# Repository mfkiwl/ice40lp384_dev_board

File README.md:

The ice30lp384_dev_board project is a multi-purpose castellated board that can be used in a breadboard or as a module in other projects.

- [Programming](/docs/Programming.md)
- [Board Creation](/docs/Board_Creation.md)

The pins on the right side of the board are geared towards programming and the pins on the left are for general use.

PCBs were ordered from OSHPark.
Stencil was ordered from OSHStencil.
Parts were ordered from Mouser, see [BOM](/docs/BOM%20-Mouser%20.xlsx).

The constraint files can be found [here](/verilog_projects/config).

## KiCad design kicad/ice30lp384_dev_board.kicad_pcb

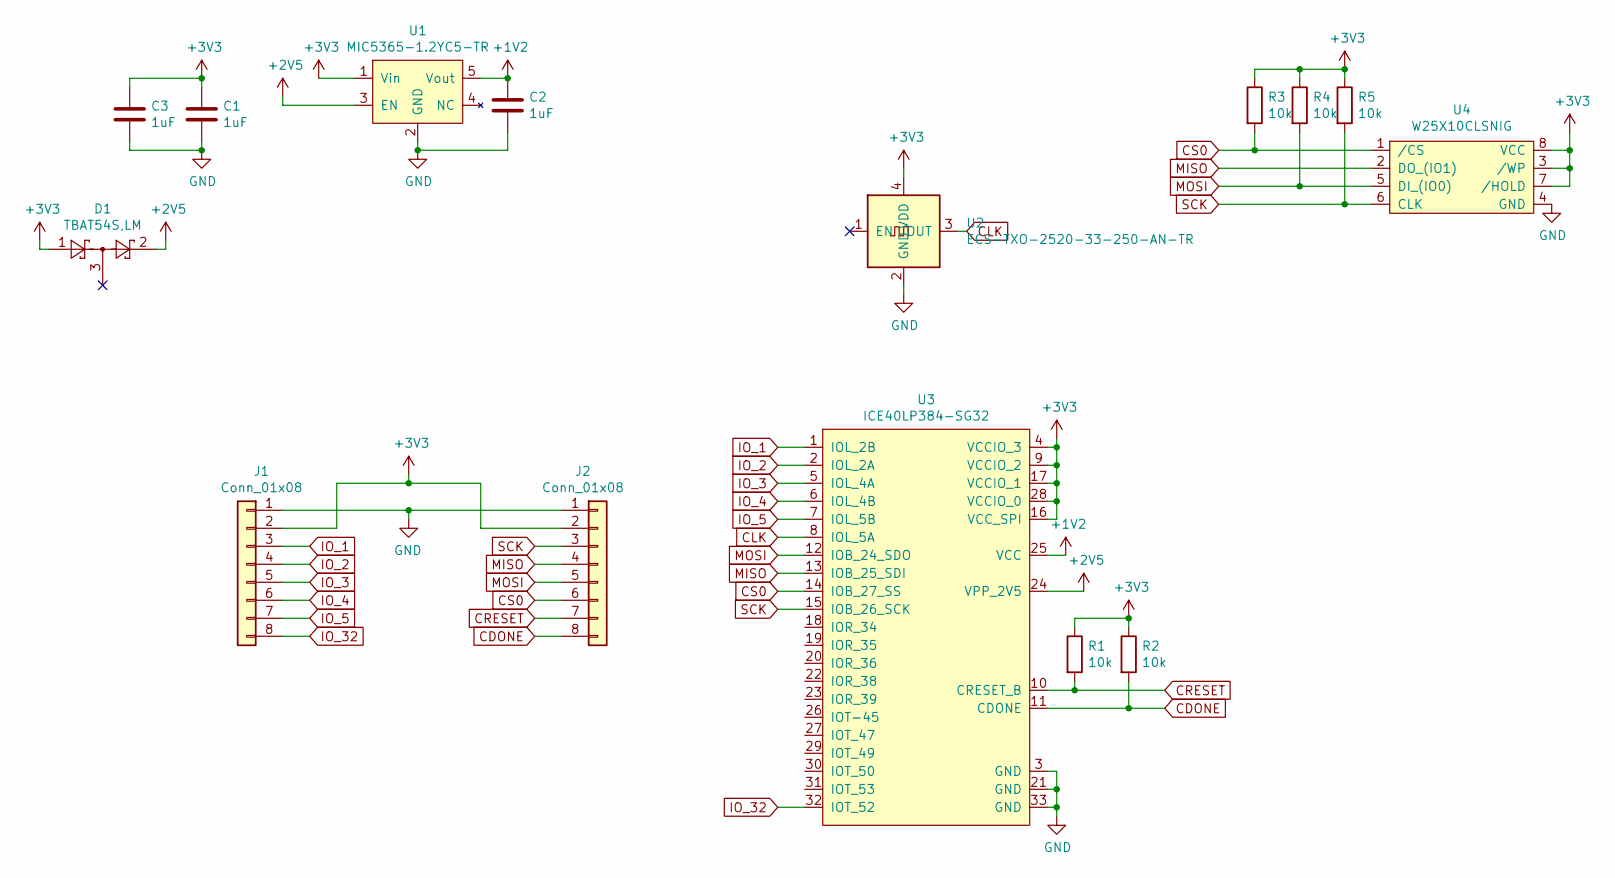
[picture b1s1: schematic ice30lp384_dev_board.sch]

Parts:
C1, C2, C3: 1uF; C_0402_1005Metric
D1: TBAT54S,LM; SOT-23
J1, J2: Conn_01x08; PinHeader_1x08_P2.54mm_Vertical
R1, R2, R3, R4, R5: 10k; R_0402_1005Metric
U1: MIC5365-1.2YC5-TR; SOT-353_SC-70-5
U2: ECS-TXO-2520-33-250-AN-TR; Oscillator_SMD_ECS_2520MV-xxx-xx-4Pin_2.5x2.0mm
U3: ICE40LP384-SG32; QFN-32-1EP_5x5mm_P0.5mm_EP3.1x3.1mm
U4: W25X10CLSNIG; SOIC-8_3.9x4.9mm_P1.27mm

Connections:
+1V2: C2.1, U1.5 (Vout), U3.25 (VCC)
+2V5: D1.2, U1.3 (EN), U3.24 (VPP_2V5)
+3V3: C1.1, C3.1, D1.1, J1.2, J2.2, R1.1, R2.1, R3.1, R4.1, R5.1, U1.1 (Vin), U2.4 (VDD), U3.4 (VCCIO_3), U3.9 (VCCIO_2), U3.16 (VCC_SPI), U3.17 (VCCIO_1), U3.28 (VCCIO_0), U4.3 (/WP), U4.7 (/HOLD), U4.8 (VCC)
CDONE: J2.8, R2.2, U3.11 (CDONE)
CLK: U2.3 (OUT), U3.8 (IOL_5A)
CRESET: J2.7, R1.2, U3.10 (CRESET_B)
CS0: J2.6, R3.2, U3.14 (IOB_27_SS), U4.1 (/CS)
GND: C1.2, C2.2, C3.2, J1.1, J2.1, U1.2 (GND), U2.2 (GND), U3.3 (GND), U3.21 (GND), U3.33 (GND), U4.4 (GND)
IO_1: J1.3, U3.1 (IOL_2B)
IO_2: J1.4, U3.2 (IOL_2A)
IO_3: J1.5, U3.5 (IOL_4A)
IO_4: J1.6, U3.6 (IOL_4B)
IO_5: J1.7, U3.7 (IOL_5B)
IO_32: J1.8, U3.32 (IOT_52)
MISO: J2.4, U3.13 (IOB_25_SDI), U4.2 (DO_(IO1))
MOSI: J2.5, R4.2, U3.12 (IOB_24_SDO), U4.5 (DI_(IO0))
SCK: J2.3, R5.2, U3.15 (IOB_26_SCK), U4.6 (CLK)

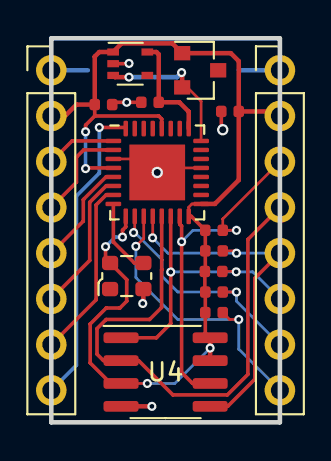
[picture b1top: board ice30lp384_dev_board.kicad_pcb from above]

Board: 2 copper layers, 12.7 x 21.3 mm, 15 parts (0 on the bottom side), 17 nets.

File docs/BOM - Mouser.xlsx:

Mfr Part Number (Input) | Quantity 1 | Mfr Part Number | Mouser Part Number | Manufacturer Name | Description | Unit Price 1 | Order Quantity | Order Unit Price | Min./Mult. | Availability | Lead Time in Days | Lead Time in Weeks | Lifecycle | NCNR | RoHS | Pb Free | Package Type | Package Quantity | Datasheet URL | Product Image | Design Risk
998-MIC5365-1.2YC5TR | 1 | MIC5365-1.2YC5-TR | 998-MIC5365-1.2YC5TR | Microchip | LDO Voltage Regulators LDO Voltage Regulators Ultra Small Single 150mA LDO | $0.12 | 1 | $0.12 | 1\1 | 13,269 | 56 | 8 |  | No | Yes | Yes | REEL | 3,000 | https://www.mouser.com/datasheet/2/268/mic5365-1082359.pdf |  | Product has high popularity and is readily available.
757-TBAT54SLM | 1 | TBAT54S,LM | 757-TBAT54SLM | Toshiba | Schottky Diodes & Rectifiers Schottky Diodes & Rectifiers Small-Signal Schotky 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 | $0.21 | 1 | $0.21 | 1\1 | 5,175 | 77 | 11 |  | No | Yes | Yes | REEL | 3,000 | https://toshiba.semicon-storage.com/info/docget.jsp?did=6654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 |  | Product has high popularity and is readily available.
842-ICE40LP384SG32 | 1 | ICE40LP384-SG32 | 842-ICE40LP384SG32 | Lattice | FPGA - Field Programmable Gate Array FPGA - Field Programmable Gate Array iCE40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 | $1.51 | 1 | $1.51 | 1\1 | 1,364 | 45 | 7 |  | No | Yes | Yes | TRAY | 490 | https://www.mouser.com/datasheet/2/225/FPGA-DS-02029-3-5-iCE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 |  | Product has high popularity and is readily available.
454-W25X10CLSNIG | 1 | W25X10CLSNIG | 454-W25X10CLSNIG | Winbond | NOR Flash NOR Flash spiFlash, 1M-bit, 4Kb Uniform Sector | $0.31 | 1 | $0.31 | 1\1 | 5,438 | 30 | 5 |  | No | Yes | Yes | TUBE | 2,000 | https://www.mouser.com/datasheet/2/949/w25x10cl_revg_021714-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 |  | Product has high popularity and is readily available.
963-EMK105BJ105MVHF | 3 | EMK105BJ105MVHF | 963-EMK105BJ105MVHF | Taiyo Yuden | Multilayer Ceramic Capacitors MLCC - SMD/SMT Multilayer Ceramic Capacitors MLCC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 | $0.10 | 3 | $0.10 | 1\1 | 57,265 | 112 | 16 | New Product | No | Yes | Yes | REEL | 10,000 | https://www.mouser.com/datasheet/2/396/taiyo_yuden_12132018_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 |  | Product is new and is readily available.
603-RC0402FR-0710KL | 5 | RC0402FR-0710KL | 603-RC0402FR-0710KL | Yageo | Thick Film Resistors - SMD Thick Film Resistors - SMD 10K OHM 1% | $0.10 | 5 | $0.10 | 1\1 | 23,214,044 | 161 | 23 |  | No | Yes | No | REEL | 10,000 | https://www.mouser.com/catalog/additional/Yageo_6012_CM_Stat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 |  | Product has high popularity and is readily available.
538-22-28-4080 | 1 | 22-28-4080 | 538-22-28-4080 | Molex | Headers & Wire Housings Headers & Wire Housings 8P VERT HEADER Sn | $0.35 | 1 | $0.35 | 1\1 | 2,976 | 28 | 4 |  | No | Yes | Yes | BULK | 6,000 | https://www.mouser.com/catalog/additional/Molex.pdf |  | Product has high popularity and is readily available.
520-2520MV-250-BN-T | 1 | ECS-2520MV-250-BN-TR | 520-2520MV-250-BN-T | ECS | Standard Clock Oscillators Standard Clock Oscillators 25MHz 1.6-3.6V -40C +85C | $0.96 | 1 | $0.96 | 1\1 | 3,019 | 84 | 12 |  | No | Yes | Yes | REEL | 3,000 | https://www.mouser.com/datasheet/2/122/ECS-2520MV-1314080.pdf |  | Product has high popularity and is readily available.

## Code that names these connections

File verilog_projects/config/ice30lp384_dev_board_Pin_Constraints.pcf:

# ##############################################################################

# iCEcube PCF

# File Generated:     Sept 27 2020 09:46:33

# Family & Device:    iCE40LP384

# Package:            QFN32

# ##############################################################################

### Main FPGA Clock
set_io i_Clk 8

### General IO:
set_io io_1 1
set_io io_2 2
set_io io_3 5
set_io io_4 6
set_io io_5 7
set_io io_7 32

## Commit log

2020-10-19 Removed ground connection from 2.5V Diode
    Updated files to change ground connection to no-connection for 2.5v diode. v1.0 boards have cut traces to prevent short to ground.
2020-10-25 Added Documentation
    Added documentation and cleaned up project structure.
    No board changes were made.
2020-10-25 Updated README
    removed layout picture from readme
2020-10-26 Update Programming.md
    Added flashrom instructions
2020-10-26 Added bitmap files
    Added bitmap files for blinky program
2020-10-26 Update Programming.md
    Changed 128M to 128k
2020-10-26 Update README.md
    Fixed typo in readme
2020-10-27 Improved castellation compatibility
    Improved compatibility with OshPark's castellation rules which involved changing all pin header pads to be round.
    Cleaned up schematic.
